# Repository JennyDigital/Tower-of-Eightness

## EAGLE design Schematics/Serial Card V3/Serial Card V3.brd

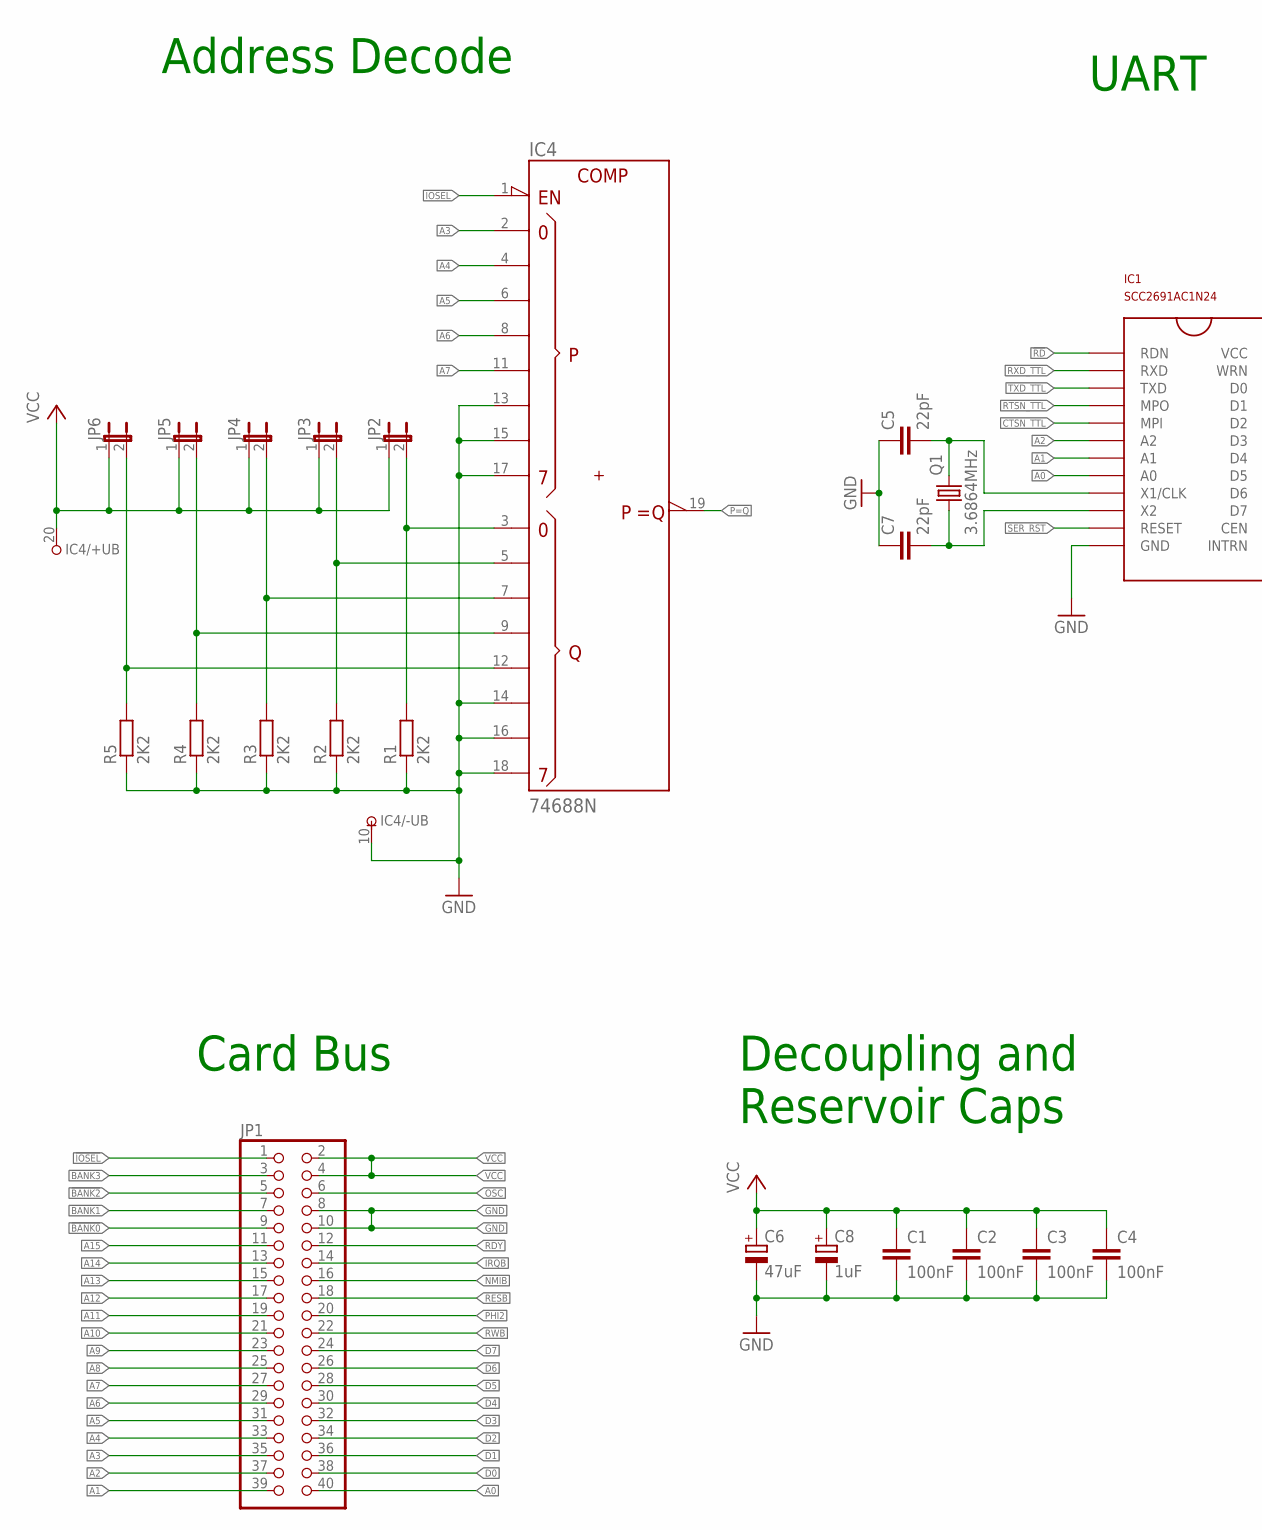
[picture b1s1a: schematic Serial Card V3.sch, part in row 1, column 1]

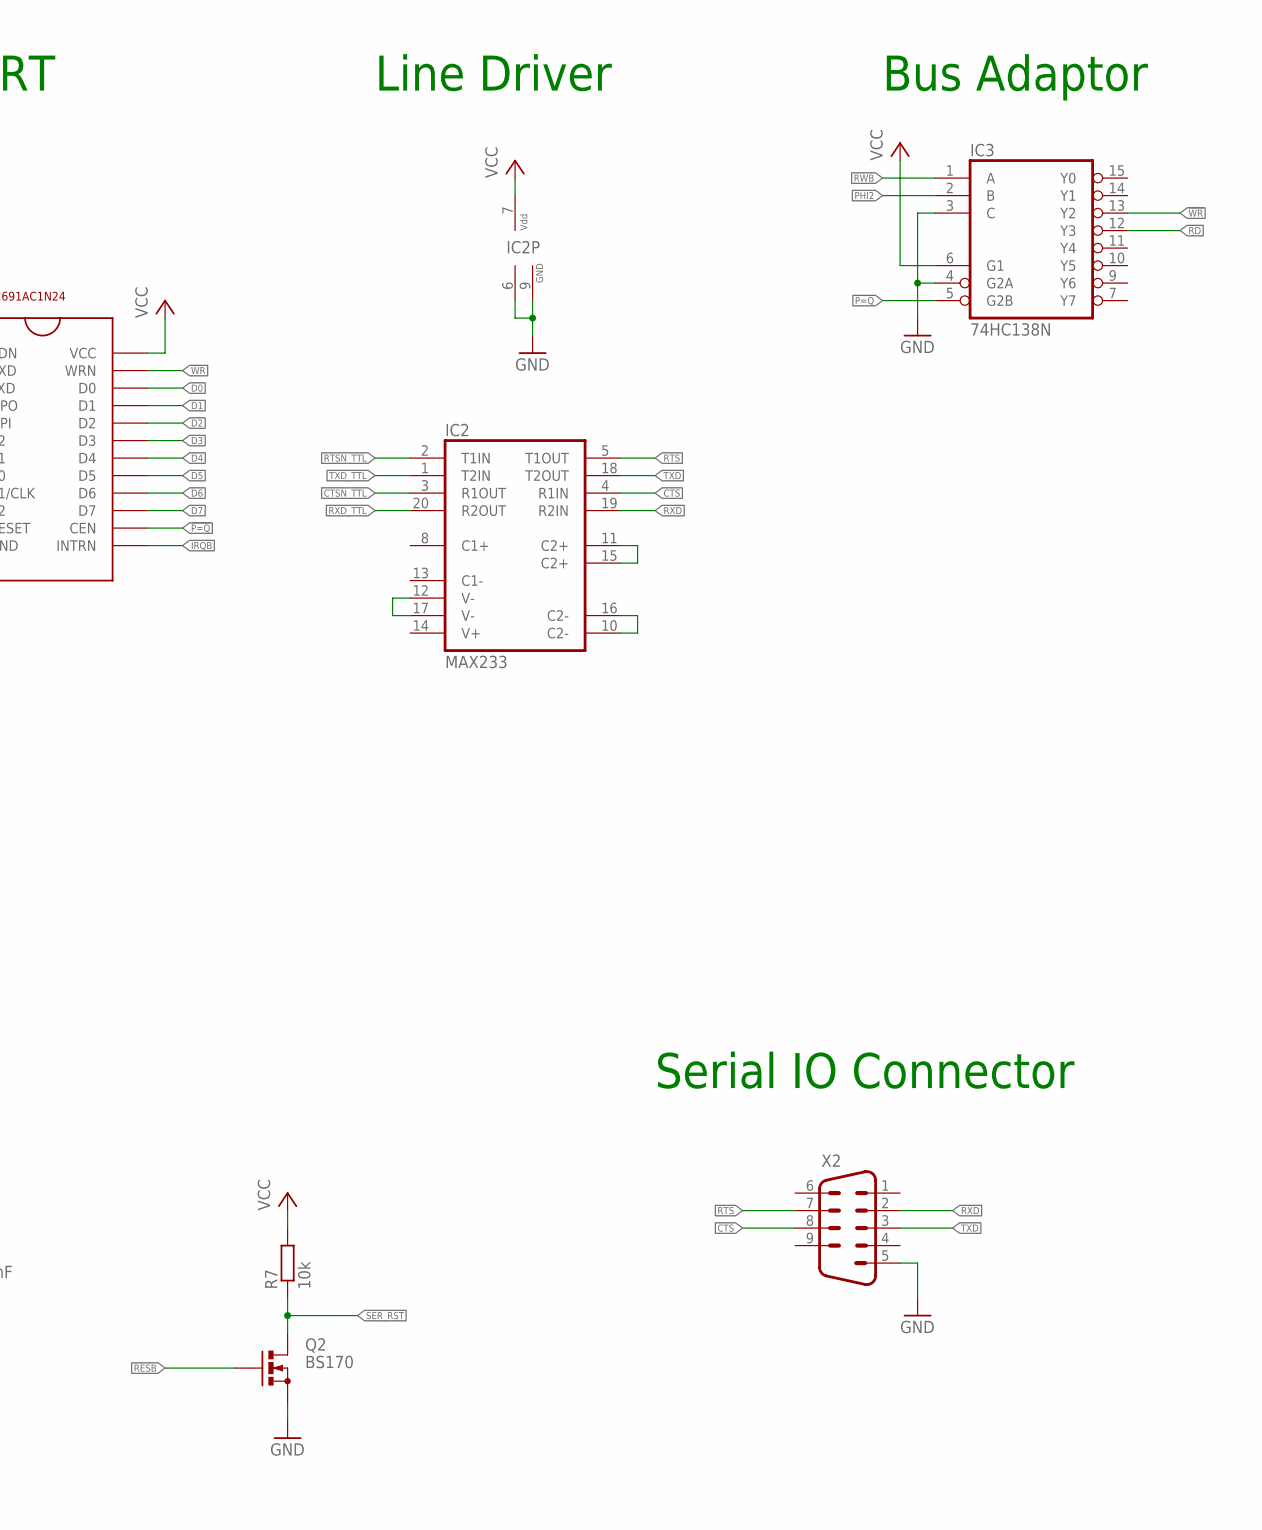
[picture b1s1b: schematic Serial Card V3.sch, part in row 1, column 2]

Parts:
C1, C2, C3, C4: 100nF; C050-025X075
C5, C7: 22pF; C025-024X044
C6: 47uF; E2,5-7
C8: 1uF; E5-5
IC1: SCC2691AC1N24; DIP
IC2: MAX233; DIL20
IC3: 74HC138N; DIL16
IC4: 74688N; DIL20
JP1: PINHD-2X20/90; 2X20/90
JP2, JP3, JP4, JP5, JP6: JP1E; JP1
Q1: 3.6864MHz; HC49/S
Q2: BS170; SOT54E
R1, R2, R3, R4, R5: 2K2; 0207/2V
R7: 10k; 0207/2V
X2: M09HP

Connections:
!BANK0: JP1.9
!BANK1: JP1.7
!BANK2: JP1.5
!BANK3: JP1.3
!IOSEL: IC4.1 (!G), JP1.1
!P=Q: IC1.CEN, IC3.5 (G2B), IC4.19 (!P=Q)
!RD: IC1.RDN, IC3.12 (Y3)
!WR: IC1.WRN, IC3.13 (Y2)
A0: IC1.A0, JP1.40
A1: IC1.A1, JP1.39
A2: IC1.A2, JP1.37
A3: IC4.2 (P0), JP1.35
A4: IC4.4 (P1), JP1.33
A5: IC4.6 (P2), JP1.31
A6: IC4.8 (P3), JP1.29
A7: IC4.11 (P4), JP1.27
A8: JP1.25
A9: JP1.23
A10: JP1.21
A11: JP1.19
A12: JP1.17
A13: JP1.15
A14: JP1.13
A15: JP1.11
CTS: IC2.4 (R1IN), X2.8
CTSN_TTL: IC1.MPI, IC2.3 (R1OUT)
D0: IC1.D0, JP1.38
D1: IC1.D1, JP1.36
D2: IC1.D2, JP1.34
D3: IC1.D3, JP1.32
D4: IC1.D4, JP1.30
D5: IC1.D5, JP1.28
D6: IC1.D6, JP1.26
D7: IC1.D7, JP1.24
GND: C1.2, C2.2, C3.2, C4.2, C5.1, C6.-, C7.1, C8.-, IC1.GND, IC2.6 (GND), IC2.9 (GND), IC3.3 (C), IC3.4 (G2A), IC3.8 (GND), IC4.10 (-UB), IC4.13 (P5), IC4.14 (Q5), IC4.15 (P6), IC4.16 (Q6), IC4.17 (P7), IC4.18 (Q7), JP1.8, JP1.10, Q2.S, R1.1, R2.1, R3.1, R4.1, R5.1, X2.5
IRQB: IC1.INTRN, JP1.14
unnamed: C5.2, IC1.X1/CLK, Q1.2
unnamed: C7.2, IC1.X2, Q1.1
unnamed: IC4.3 (Q0), JP2.2, R1.2
unnamed: IC4.5 (Q1), JP3.2, R2.2
unnamed: IC4.7 (Q2), JP4.2, R3.2
unnamed: IC4.9 (Q3), JP5.2, R4.2
unnamed: IC4.12 (Q4), JP6.2, R5.2
unnamed: IC2.11 (C2+), IC2.15 (C2+)
unnamed: IC2.10 (C2-), IC2.16 (C2-)
unnamed: IC2.12 (V-), IC2.17 (V-)
NMIB: JP1.16
OSC: JP1.6
PHI2: IC3.2 (B), JP1.20
RDY: JP1.12
RESB: JP1.18, Q2.G
RTS: IC2.5 (T1OUT), X2.7
RTSN_TTL: IC1.MPO, IC2.2 (T1IN)
RWB: IC3.1 (A), JP1.22
RXD: IC2.19 (R2IN), X2.2
RXD_TTL: IC1.RXD, IC2.20 (R2OUT)
SER_RST: IC1.RESET, Q2.D, R7.1
TXD: IC2.18 (T2OUT), X2.3
TXD_TTL: IC1.TXD, IC2.1 (T2IN)
VCC: C1.1, C2.1, C3.1, C4.1, C6.+, C8.+, IC1.VCC, IC2.7 (VDD), IC3.6 (G1), IC3.16 (VCC), IC4.20 (+UB), JP1.2, JP1.4, JP2.1, JP3.1, JP4.1, JP5.1, JP6.1, R7.2

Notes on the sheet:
Card Bus
Decoupling and Reservoir Caps
Serial IO Connector
Address Decode
UART
Line Driver
Bus Adaptor

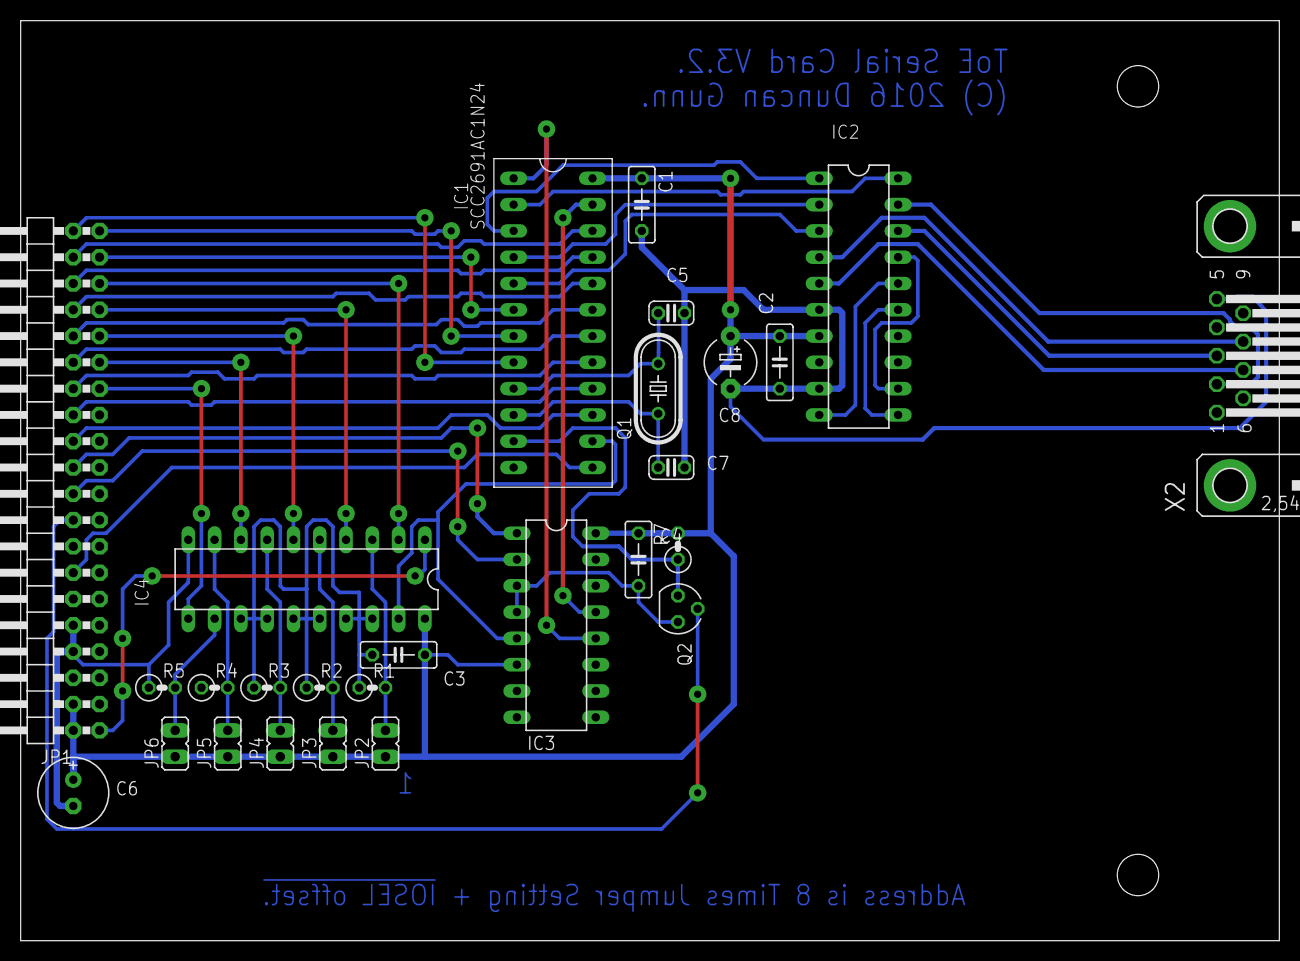
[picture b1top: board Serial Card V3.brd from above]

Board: 2 copper layers, 121.6 x 88.9 mm, 27 parts (0 on the bottom side), 45 nets.

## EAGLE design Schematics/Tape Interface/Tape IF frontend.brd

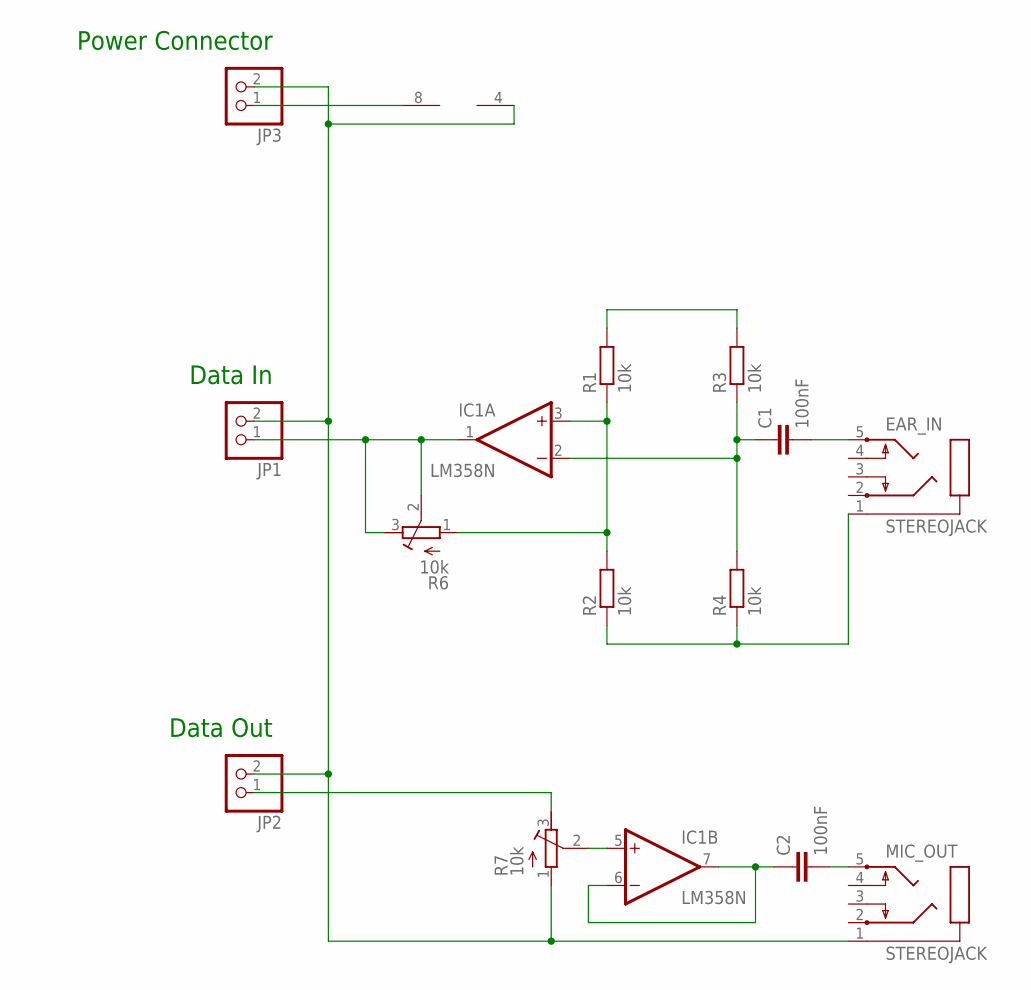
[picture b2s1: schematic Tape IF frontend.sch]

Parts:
C1, C2: 100nF; C050-025X075
EAR_IN: STEREOJACK; STX3100
IC1: LM358N; DIL08
JP1, JP2, JP3: PINHD-1X2; 1X02
MIC_OUT: STEREOJACK; STX3100
R1, R2, R3, R4: 10k; 0207/10
R6, R7: 10k; RTRIM64W

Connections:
+5V: IC1.8 (V+), JP3.1
BUFFERED_OUT: C2.2, MIC_OUT.5
EAR_SCHMITTED: IC1.1 (OUT), JP1.1, R6.2 (S), R6.3 (E)
GND: IC1.4 (V-), JP1.2, JP2.2, JP3.2, MIC_OUT.1, R7.1 (A)
unnamed: C1.2, EAR_IN.5
unnamed: C1.1, IC1.2 (-IN), R3.1, R4.2
unnamed: IC1.3 (+IN), R1.1, R2.2, R6.1 (A)
unnamed: EAR_IN.1, R2.1, R4.1
unnamed: R1.2, R3.2
unnamed: C2.1, IC1.6 (-IN), IC1.7 (OUT)
unnamed: IC1.5 (+IN), R7.2 (S)
UNBUFFERED_OUT: JP2.1, R7.3 (E)

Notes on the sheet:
Power Connector
Data In
Data Out

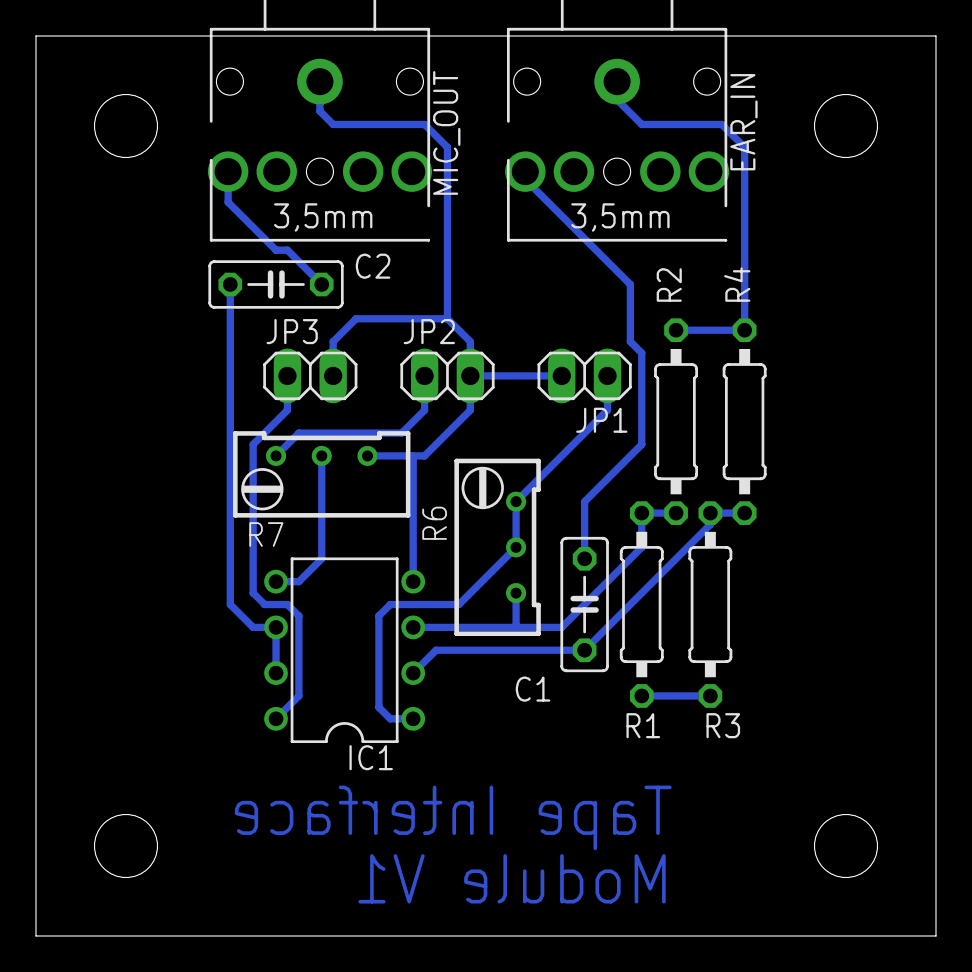
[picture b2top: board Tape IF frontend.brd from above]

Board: 2 copper layers, 50.0 x 50.0 mm, 14 parts (0 on the bottom side), 12 nets.

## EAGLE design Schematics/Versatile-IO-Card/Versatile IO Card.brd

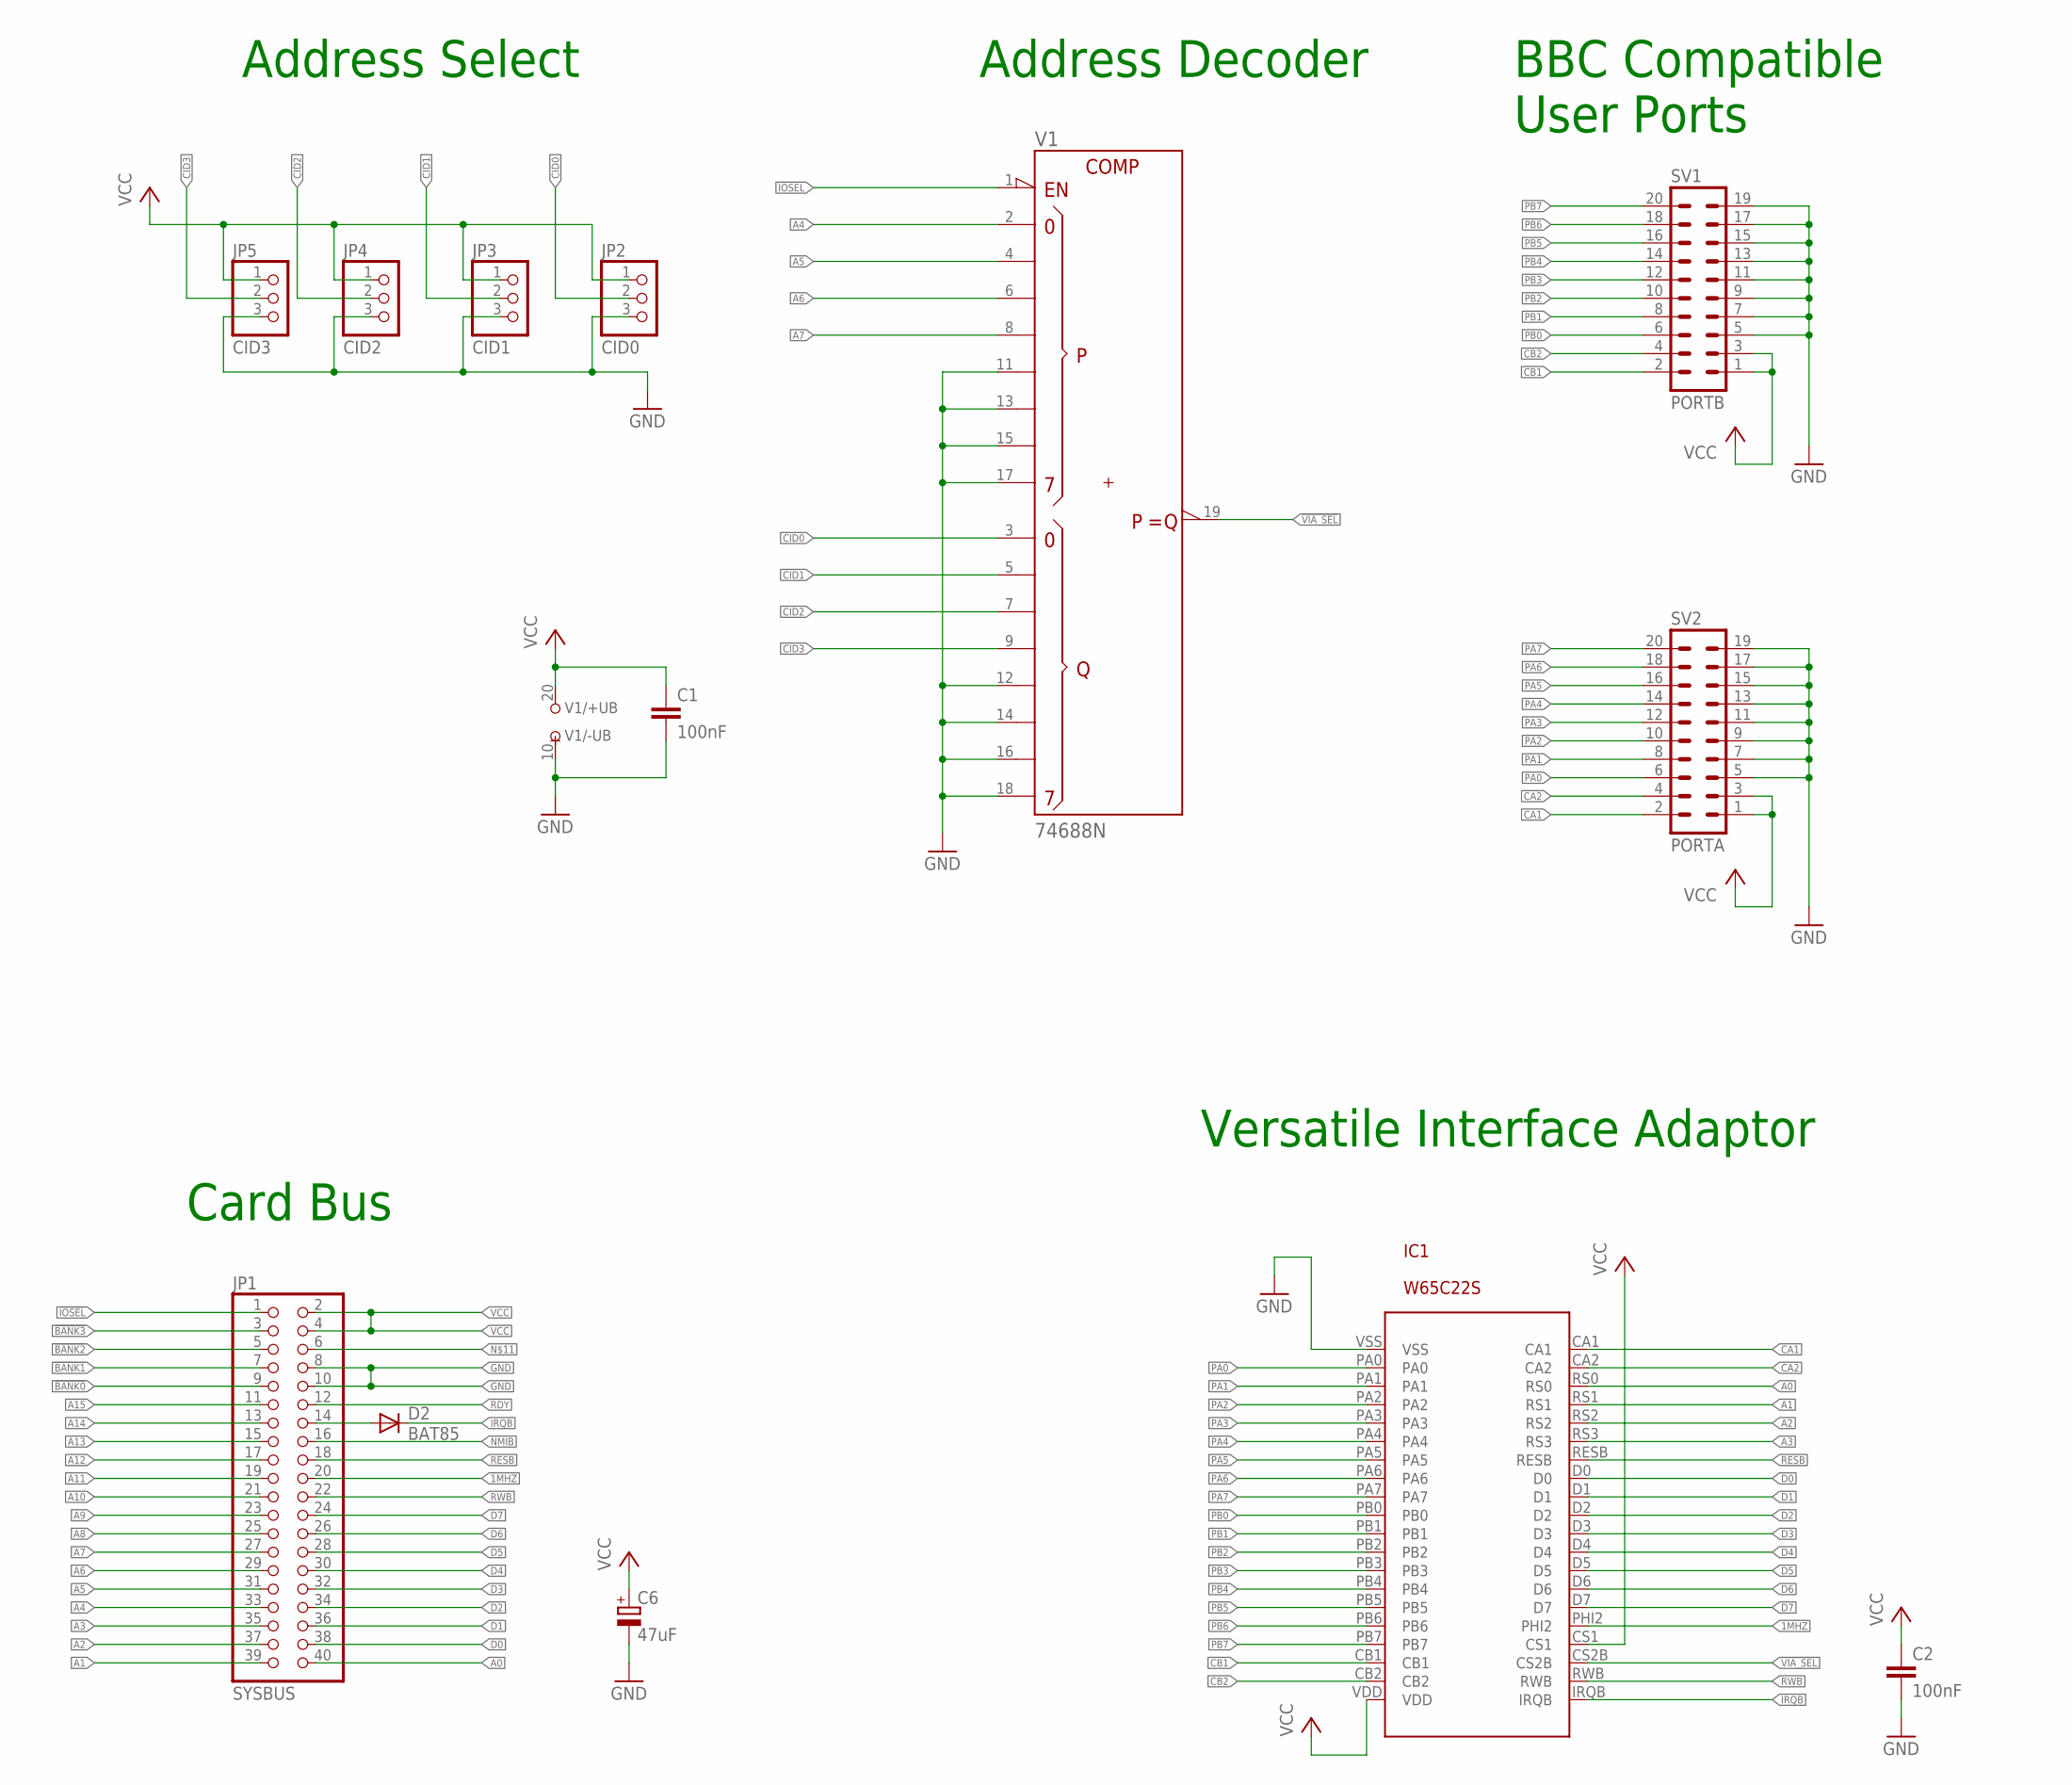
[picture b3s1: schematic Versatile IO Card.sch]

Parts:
C1, C2: 100nF; C050-025X075
C6: 47uF; E2,5-7
D2: BAT85; DO34-7
IC1: W65C22S; W65C22-DIP
JP1: SYSBUS; 2X20/90
JP2: CID0; 1X03
JP3: CID1; 1X03
JP4: CID2; 1X03
JP5: CID3; 1X03
SV1: PORTB; ML20L
SV2: PORTA; ML20L
V1: 74688N; DIL20

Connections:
1MHZ: IC1.PHI2, JP1.20
!BANK0: JP1.9
!BANK1: JP1.7
!BANK2: JP1.5
!BANK3: JP1.3
!IOSEL: JP1.1, V1.1 (!G)
!VIA_SEL: IC1.CS2B, V1.19 (!P=Q)
A0: IC1.RS0, JP1.40
A1: IC1.RS1, JP1.39
A2: IC1.RS2, JP1.37
A3: IC1.RS3, JP1.35
A4: JP1.33, V1.2 (P0)
A5: JP1.31, V1.4 (P1)
A6: JP1.29, V1.6 (P2)
A7: JP1.27, V1.8 (P3)
A8: JP1.25
A9: JP1.23
A10: JP1.21
A11: JP1.19
A12: JP1.17
A13: JP1.15
A14: JP1.13
A15: JP1.11
CA1: IC1.CA1, SV2.2
CA2: IC1.CA2, SV2.4
CB1: IC1.CB1, SV1.2
CB2: IC1.CB2, SV1.4
CID0: JP2.2, V1.3 (Q0)
CID1: JP3.2, V1.5 (Q1)
CID2: JP4.2, V1.7 (Q2)
CID3: JP5.2, V1.9 (Q3)
D0: IC1.D0, JP1.38
D1: IC1.D1, JP1.36
D2: IC1.D2, JP1.34
D3: IC1.D3, JP1.32
D4: IC1.D4, JP1.30
D5: IC1.D5, JP1.28
D6: IC1.D6, JP1.26
D7: IC1.D7, JP1.24
GND: C1.2, C2.2, C6.-, IC1.VSS, JP1.8, JP1.10, JP2.3, JP3.3, JP4.3, JP5.3, SV1.5, SV1.7, SV1.9, SV1.11, SV1.13, SV1.15, SV1.17, SV1.19, SV2.5, SV2.7, SV2.9, SV2.11, SV2.13, SV2.15, SV2.17, SV2.19, V1.10 (-UB), V1.11 (P4), V1.12 (Q4), V1.13 (P5), V1.14 (Q5), V1.15 (P6), V1.16 (Q6), V1.17 (P7), V1.18 (Q7)
IRQB: D2.C, IC1.IRQB
unnamed: D2.A, JP1.14
NMIB: JP1.16
PA0: IC1.PA0, SV2.6
PA1: IC1.PA1, SV2.8
PA2: IC1.PA2, SV2.10
PA3: IC1.PA3, SV2.12
PA4: IC1.PA4, SV2.14
PA5: IC1.PA5, SV2.16
PA6: IC1.PA6, SV2.18
PA7: IC1.PA7, SV2.20
PB0: IC1.PB0, SV1.6
PB1: IC1.PB1, SV1.8
PB2: IC1.PB2, SV1.10
PB3: IC1.PB3, SV1.12
PB4: IC1.PB4, SV1.14
PB5: IC1.PB5, SV1.16
PB6: IC1.PB6, SV1.18
PB7: IC1.PB7, SV1.20
RDY: JP1.12
RESB: IC1.RESB, JP1.18
RWB: IC1.RWB, JP1.22
VCC: C1.1, C2.1, C6.+, IC1.CS1, IC1.VDD, JP1.2, JP1.4, JP2.1, JP3.1, JP4.1, JP5.1, SV1.1, SV1.3, SV2.1, SV2.3, V1.20 (+UB)

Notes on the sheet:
Card Bus
Address Select
Address Decoder
BBC Compatible User Ports
Versatile Interface Adaptor

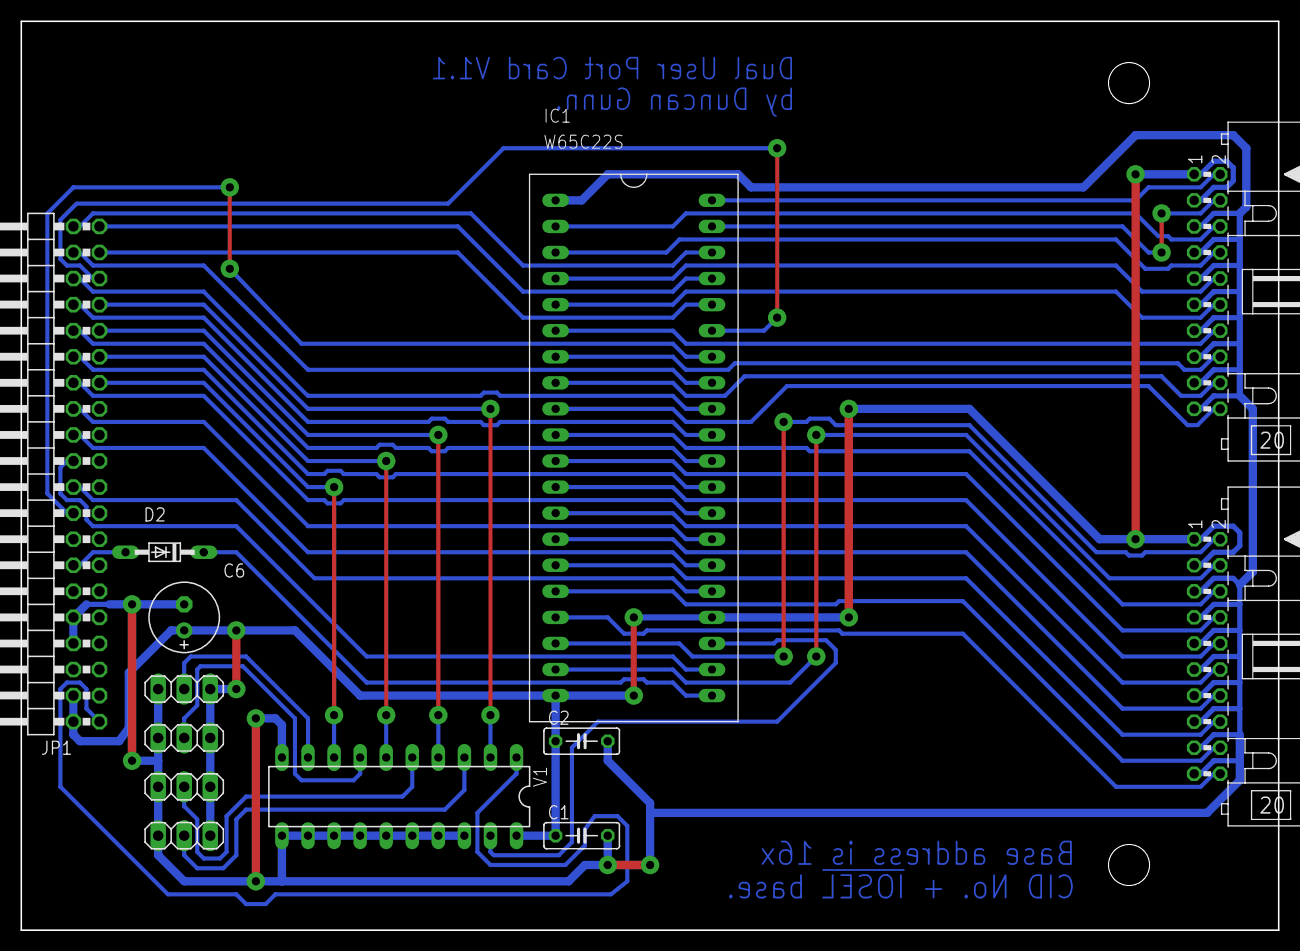
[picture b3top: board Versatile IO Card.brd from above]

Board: 2 copper layers, 122.5 x 88.6 mm, 13 parts (0 on the bottom side), 49 nets.

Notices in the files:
Schematics/Serial Card V3/Serial Card V3.brd:
(C) 2016 Duncan Gunn.
